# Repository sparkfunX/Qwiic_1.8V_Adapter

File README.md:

SparkFun Qwiic 1.8V adapter
========================================

[*SparkFun Part Name (SKU)*](URL for product on Sparkfun.com)

The Qwiic 1.8V Adapter does what it says on the box: Adapts 1.8V sensors to work with the Qwiic system! 
It does this using the PCA9306 dual bidirectional I2C voltage-level translator for the data lines alongside a small 300mA LDO for the power. 

Repository Contents
-------------------

* **/Documentation** - Data sheets, additional product information
* **/Hardware** - Eagle design files (.brd, .sch)
* **/Production** - Production panel files (.brd)

License Information
-------------------

This product is _**open source**_! 

Please review the LICENSE.md file for license information. 

If you have any questions or concerns on licensing, please contact technical support on our [SparkFun forums](https://forum.sparkfun.com/viewforum.php?f=152).

Distributed as-is; no warranty is given.

- Your friends at SparkFun.

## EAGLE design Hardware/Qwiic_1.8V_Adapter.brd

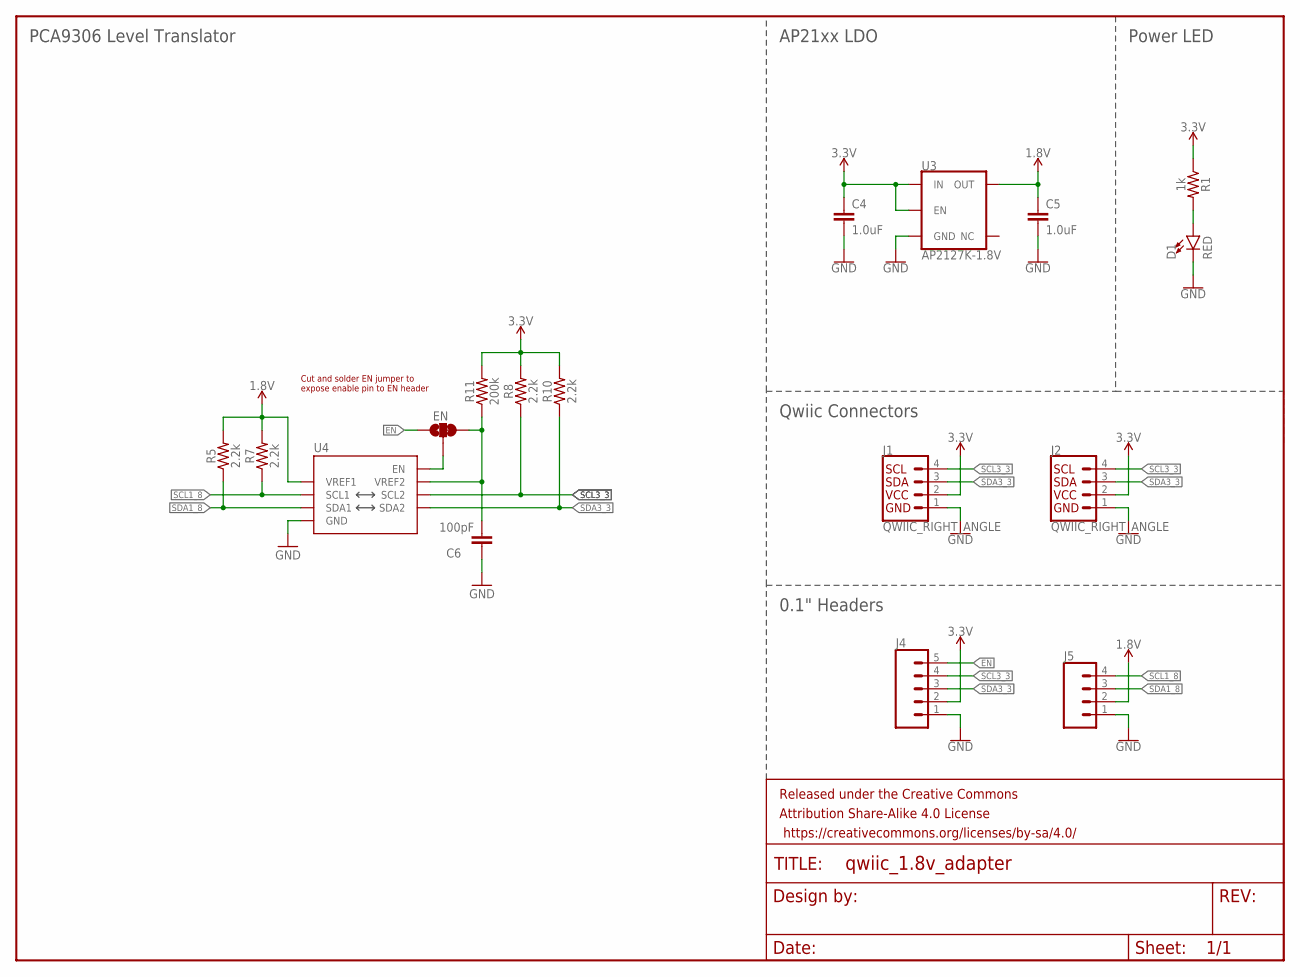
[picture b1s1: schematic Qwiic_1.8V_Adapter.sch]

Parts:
C4, C5: 1.0uF; 0603
C6: 100pF; 0603
D1: RED; LED-0603
EN: JUMPER-SMT_3_1-NC_TRACE_SILK; SMT-JUMPER_3_1-NC_TRACE_SILK
FRAME1: FRAME-LETTER; CREATIVE_COMMONS
J1, J2: QWIIC_RIGHT_ANGLE; JST04_1MM_RA
J4: CONN_05NO_SILK; 1X05_NO_SILK
J5: CONN_041X04_NO_SILK; 1X04_NO_SILK
R1: 1k; 0603
R5, R7, R8, R10: 2.2k; 0603
R11: 200k; 0603
U3: AP2127K-1.8V; SOT23-5
U4: PCA9306VSSOP_8PIN; VSSOP_8PIN

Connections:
1.8V: C5.1, J5.2, R5.2, R7.2, U3.5 (OUT), U4.P2 (VREF1)
3.3V: C4.1, J1.2, J2.2, J4.2, R1.1, R8.2, R10.2, R11.2, U3.1 (IN), U3.3 (EN)
EN: EN.1, J4.5
GND: C4.2, C5.2, C6.1, D1.C, J1.1, J2.1, J4.1, J5.1, U3.2 (GND), U4.P1 (GND)
unnamed: EN.2, U4.P8 (EN)
unnamed: D1.A, R1.2
unnamed: C6.2, EN.3, R11.1, U4.P7 (VREF2)
SCL1_8: J5.4, R7.1, U4.P3 (SCL1)
SCL3_3: J1.4, J2.4, J4.4, R8.1, U4.P6 (SCL2)
SDA1_8: J5.3, R5.1, U4.P4 (SDA1)
SDA3_3: J1.3, J2.3, J4.3, R10.1, U4.P5 (SDA2)

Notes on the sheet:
PCA9306 Level Translator
AP21xx LDO
Power LED
Qwiic Connectors
0.1" Headers
Cut and solder EN jumper to expose enable pin to EN header

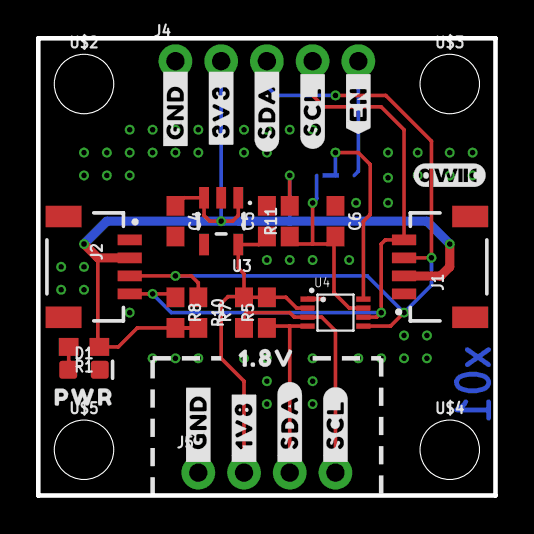
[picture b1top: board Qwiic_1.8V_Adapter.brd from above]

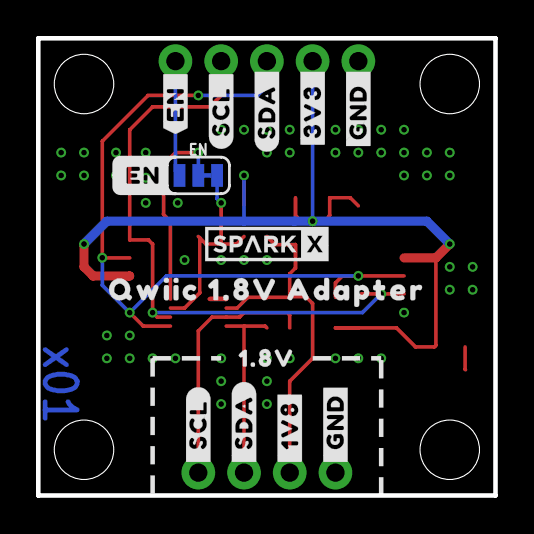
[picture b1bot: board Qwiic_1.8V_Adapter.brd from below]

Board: 2 copper layers, 25.4 x 25.4 mm, 47 parts (14 on the bottom side), 11 nets.

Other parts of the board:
U$1, U$17: #_GND#0
U$2, U$3, U$4, U$5: STAND-OFF
U$6, U$18: #_1V8#0
U$7, U$19: #_SDA#0
U$8, U$20: #_SCL#0
U$9: PWR0
U$10, U$21: #GND_#0
U$11, U$22: #3V3_#0
U$12, U$23: #SDA_#0
U$13, U$24: #SCL_#0
U$14, U$25: #EN_#0
U$15, U$26: 1#8V0
U$16: QWIIC_4MM
U$27: #EN#0
U$28: QWIIC_1#8V_ADAPTER0
U$29: SPARKX-SMALL

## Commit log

2021-11-10 x01 pre review
2021-11-10 Add EN Jumper note
2022-02-10 Production Files and README

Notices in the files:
parts and their libraries:
SparkFun-Capacitors: Licensing: CC v3.0 Share-Alike You are welcome to use this library for commercial purposes.
SparkFun-Aesthetics: Licensing: Creative Commons ShareAlike 4.0 International - https://creativecommons.org/licenses/by-sa/4.0
SparkFun-Aesthetics: Released under the Creative Commons
